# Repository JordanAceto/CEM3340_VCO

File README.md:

# CEM3340 based VCO PCB

## Features:
- Sine, Triangle, Sawtooth, and variable Pulse waves simultaneously available.
- All waveforms +/- 5vpp.
- Three 1 volt/octave inputs, linear FM, sync (choose hard or soft), and PWM modulation inputs.
- Onboard voltage regulators and reference voltage generators for stable tuning.
- Input voltage can be either +/- 12 volts DC, or +/- 15 volts DC.
- Designed to either plug into a separate carrier pcb with pots and jacks, or mount to a bracket and wire by hand. 

## A note about the pulse waveform:
 This design does not use the built in CEM3340 pulse generator. Instead, an typical opamp circuit is used for the Pulse wave output. This is to avoid the influence of PWM on the frequency of the oscillator, which has been reported to be a problem, especially with the AS3340 versions of the chip. The built in pulse generator is disabled by tying the output to ground through a resistor, and hardwiring a negative voltage into pin 5 which permanently sets the pulse width to zero percent.

## Status of the project:

Revision | breadboarded | schematic | pcb layout | built and tested | documentation
---------|--------------|-----------|------------|------------------|---------------
1        | &#9745;      | &#9745;   | &#9745;    | &#9745;          | &#9745; 

## Informal evaluation:

I've built three of these, and they work well and are fairly easy to build. The dual NPN in the sine shaper is a little small, but after doing a few of them I can solder them reliably without any grief.

Calibration is pretty straightforward and they tune up nicely and don't drift badly with changes in temperature. I have not done any rigorous testing, just by-ear, but I'm pretty picky about out of tune VCOs and these seem good to me so far.

Overall quite happy with this VCO.

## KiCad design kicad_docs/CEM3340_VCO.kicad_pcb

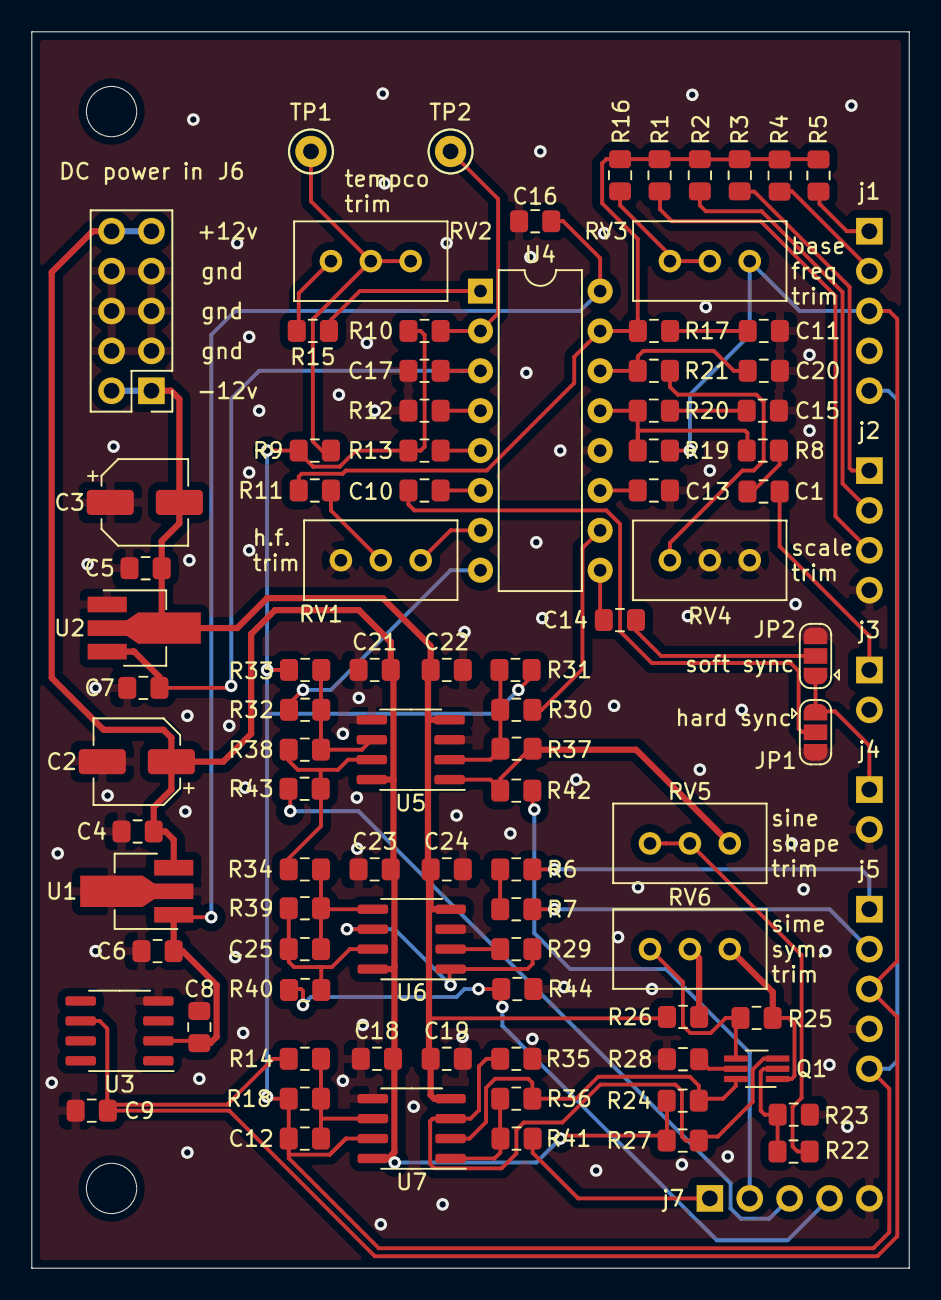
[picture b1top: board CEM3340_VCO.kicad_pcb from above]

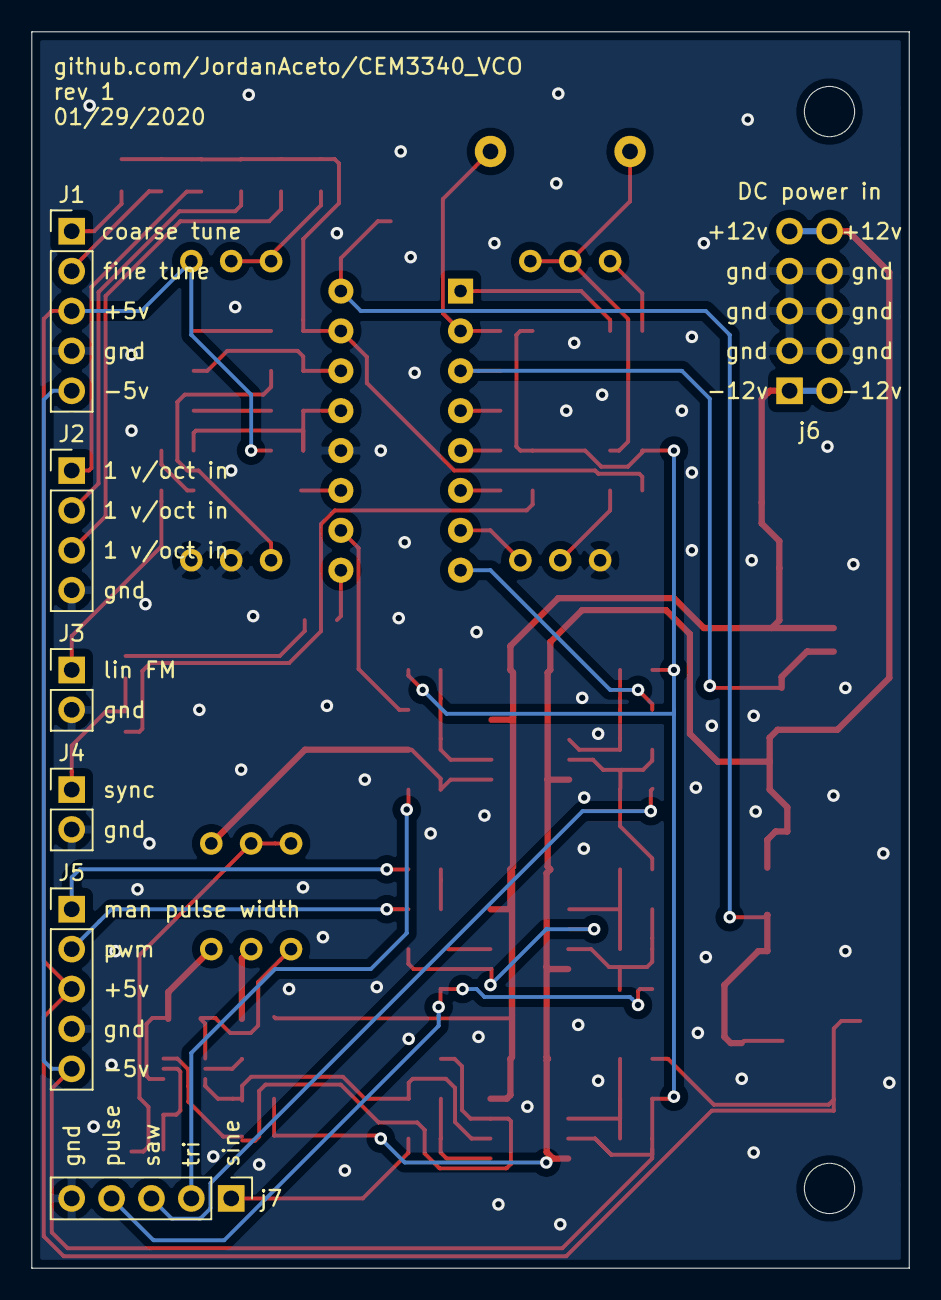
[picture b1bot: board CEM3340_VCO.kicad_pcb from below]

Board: 2 copper layers, 55.9 x 78.7 mm, 96 parts (6 on the bottom side), 62 nets.

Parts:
C1, C4, C5, C6, C7, C8, C9, C12, C16, C17, C18, C19, C21, C22, C23, C24: 100nF; C_0805_2012Metric_Pad1.15x1.40mm_HandSolder
C2, C3: 10uF; CP_Elec_5x5.4
C10, C13, C14: 1nF; C_0805_2012Metric_Pad1.15x1.40mm_HandSolder
C11, C15: 10nF; C_0805_2012Metric_Pad1.15x1.40mm_HandSolder
C20: 560pF; C_0805_2012Metric_Pad1.15x1.40mm_HandSolder
C25: 10pF; C_0805_2012Metric_Pad1.15x1.40mm_HandSolder
H1, H2: MountingHole; MountingHole_3.2mm_M3
J1: tuning controls; PinHeader_1x05_P2.54mm_Vertical
J2: 1 v/oct inputs; PinHeader_1x04_P2.54mm_Vertical
J3: linear FM input; PinHeader_1x02_P2.54mm_Vertical
J4: sync input; PinHeader_1x02_P2.54mm_Vertical
J5: PWM inputs; PinHeader_1x05_P2.54mm_Vertical
J6: power input; PinHeader_2x05_P2.54mm_Vertical
JP1: sync sel 1; SolderJumper-3_P1.3mm_Open_RoundedPad1.0x1.5mm
JP2: sync sel 2; SolderJumper-3_P1.3mm_Open_RoundedPad1.0x1.5mm
Q1: MMDT3904; SOT-363_SC-70-6_Handsoldering
R1, R2, R3, R5, R7, R29, R31, R33, R37, R38: 100k; R_0805_2012Metric_Pad1.15x1.40mm_HandSolder
R4, R8, R11: 1M; R_0805_2012Metric_Pad1.15x1.40mm_HandSolder
R6: 110k; R_0805_2012Metric_Pad1.15x1.40mm_HandSolder
R9, R10: 5k6; R_0805_2012Metric_Pad1.15x1.40mm_HandSolder
R12, R13: 51k; R_0805_2012Metric_Pad1.15x1.40mm_HandSolder
R14, R18, R24, R27, R34: 10k; R_0805_2012Metric_Pad1.15x1.40mm_HandSolder
R15, R26: 18k; R_0805_2012Metric_Pad1.15x1.40mm_HandSolder
R16: 82k; R_0805_2012Metric_Pad1.15x1.40mm_HandSolder
R17, R20: 470; R_0805_2012Metric_Pad1.15x1.40mm_HandSolder
R19: 680k; R_0805_2012Metric_Pad1.15x1.40mm_HandSolder
R21: 1k62; R_0805_2012Metric_Pad1.15x1.40mm_HandSolder
R22: 27k; R_0805_2012Metric_Pad1.15x1.40mm_HandSolder
R23, R28: 2k2; R_0805_2012Metric_Pad1.15x1.40mm_HandSolder
R25: 390; R_0805_2012Metric_Pad1.15x1.40mm_HandSolder
R30: 34k; R_0805_2012Metric_Pad1.15x1.40mm_HandSolder
R32: 68k; R_0805_2012Metric_Pad1.15x1.40mm_HandSolder
R35, R36: 15k; R_0805_2012Metric_Pad1.15x1.40mm_HandSolder
R39: 10M; R_0805_2012Metric_Pad1.15x1.40mm_HandSolder
R40, R44: 2k; R_0805_2012Metric_Pad1.15x1.40mm_HandSolder
R41, R42, R43: 1k; R_0805_2012Metric_Pad1.15x1.40mm_HandSolder
RV1: 20k; Potentiometer_Bourns_3296W_Vertical
RV2: 5k; Potentiometer_Bourns_3296W_Vertical
RV3, RV5, RV6: 50k; Potentiometer_Bourns_3296W_Vertical
RV4: 500; Potentiometer_Bourns_3296W_Vertical
TP1, TP2: TestPoint; TestPoint_Keystone_5000-5004_Miniature
U1: L78L10_SOT89; SOT-89-3_Handsoldering
U2: MC7905; SOT-89-3_Handsoldering
U3: REF02AU; SOIC-8_3.9x4.9mm_P1.27mm
U4: CEM3340; DIP-16_W7.62mm
U5, U6, U7: TL072; SOIC-8_3.9x4.9mm_P1.27mm
j7: waveform outputs; PinHeader_1x05_P2.54mm_Vertical

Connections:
+5VA: C9.2, J1.3, J5.3, R14.2, R19.1, RV3.3, U3.6
+10V: C6.2, C8.2, C16.1, U1.1, U3.2, U4.16
+15V: C2.1, C4.1, C18.1, C21.1, C23.1, J6.9, J6.10, R24.1, R27.1, U1.3, U5.8, U6.8, U7.8
-5V: C7.1, C17.2, U2.3, U4.3
-5VA: C12.1, J1.5, J5.5, R9.2, R10.2, R13.2, R18.1, R31.2, R33.2, U7.7
-15V: C3.2, C5.2, C19.2, C22.2, C24.2, J6.1, J6.2, R26.2, U2.2, U5.4, U6.4, U7.4
/Signal_Inputs/expo_cv_i_out: R1.1, R2.1, R3.1, R4.1, R5.1, R11.2, R16.2, R17.2, U4.15
/Signal_Inputs/lin_cv_i_out: R8.1, R19.2, R20.2, U4.13
/Signal_Inputs/pulse_width_i_out: R6.1, R7.1
/VCO_Core/hard_sync_v_in: C10.2, JP1.2
/VCO_Core/soft_sync_v_in: C14.1, JP2.2
/Waveshapers/10vpp_pulse_v_out: R40.1, R44.1, j7.4
/Waveshapers/10vpp_saw_v_out: R43.1, j7.3
/Waveshapers/10vpp_sine_v_out: R41.1, j7.1
/Waveshapers/10vpp_triangle_v_out: R42.1, j7.2
/Waveshapers/raw_saw_v_in: R32.2, U4.8
/Waveshapers/raw_triangle_v_in: R30.2, U4.10
GND: C2.2, C3.1, C4.2, C5.1, C6.1, C7.2, C8.1, C9.1, C11.2, C13.1, C15.2, C16.2, C17.1, C18.2, C19.1, C20.2, C21.2, C22.1, C23.2, C24.1, J1.4, J2.4, J3.2, J4.2, J5.4, J6.3, J6.4, J6.5, J6.6, J6.7, J6.8, JP1.3, JP2.3, R12.2, R23.1, R28.1, R35.1, R44.2, RV1.1, RV4.1, RV4.2, U1.2, U2.1, U3.4, U4.12, U5.3, U5.5, U6.3, U7.5, j7.5
unnamed: C1.1, R8.2
unnamed: C1.2, J3.1
unnamed: C10.1, U4.6
unnamed: C11.1, R17.1
unnamed: C12.2, R14.1, R18.2, U7.6
unnamed: C13.2, U4.11
unnamed: C14.2, U4.9
unnamed: C15.1, R20.1
unnamed: C20.1, R21.1, U4.14
unnamed: C25.1, R39.1, R40.2, U6.7
unnamed: C25.2, R34.1, R39.2, U6.5
unnamed: J1.1, R5.2
unnamed: J1.2, R4.2
unnamed: J2.1, R3.2
unnamed: J2.2, R2.2
unnamed: J2.3, R1.2
unnamed: J4.1, JP1.1, JP2.1
unnamed: J5.1, R6.2
unnamed: J5.2, R7.2
unnamed: Q1.1, R25.1, RV6.3
unnamed: Q1.2, R22.1, R23.2
unnamed: Q1.3, R27.2, R35.2, U7.3
unnamed: Q1.4, R25.2, RV6.1
unnamed: Q1.5, R28.2
unnamed: Q1.6, R24.2, R36.2, U7.2
unnamed: R9.1, RV2.1, RV2.2, TP1.1
unnamed: R10.1, TP2.1, U4.2
unnamed: R11.1, RV1.2
unnamed: R12.1, U4.4
unnamed: R13.1, U4.5
unnamed: R15.1, U4.1
unnamed: R15.2, RV2.3
unnamed: R16.1, RV3.1, RV3.2
unnamed: R21.2, RV4.3
unnamed: R22.2, RV5.1, RV5.2
unnamed: R26.1, RV6.2
unnamed: R29.1, U6.1, U6.6
unnamed: R29.2, U6.2
unnamed: R30.1, R31.1, R37.2, U5.2
unnamed: R32.1, R33.1, R38.2, U5.6
unnamed: R34.2, R38.1, R43.2, U5.7
unnamed: R36.1, R41.2, U7.1
unnamed: R37.1, R42.2, RV5.3, U5.1
unnamed: RV1.3, U4.7

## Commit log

2020-01-29 initial commit, schem and pcb underway, not final
2020-01-29 add dir for pics
2020-01-29 place github url on pcb silk
2020-01-29 add rudimentary README
2020-01-29 move description to top in readme
2020-01-29 Create LICENSE
2020-01-29 add license to readme
2020-01-29 add warning to readme
2020-01-29 generate gerbers
2020-01-29 change mounting holes to pth
2020-01-29 regenerate BOM, better but not done
2020-01-30 extract circuit blocks into separate schem pages
2020-01-30 add pdf schematic
2020-02-15 update and fill in some resistor values
2020-02-15 update pdf schematic with new resistor values
2020-02-15 increase sine level to 10vpp
2020-05-29 remove readme warning
2020-08-06 finalize some values, update documentation
